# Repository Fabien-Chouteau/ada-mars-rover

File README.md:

This project now lives at https://github.com/AdaCore/mars-rover-demo

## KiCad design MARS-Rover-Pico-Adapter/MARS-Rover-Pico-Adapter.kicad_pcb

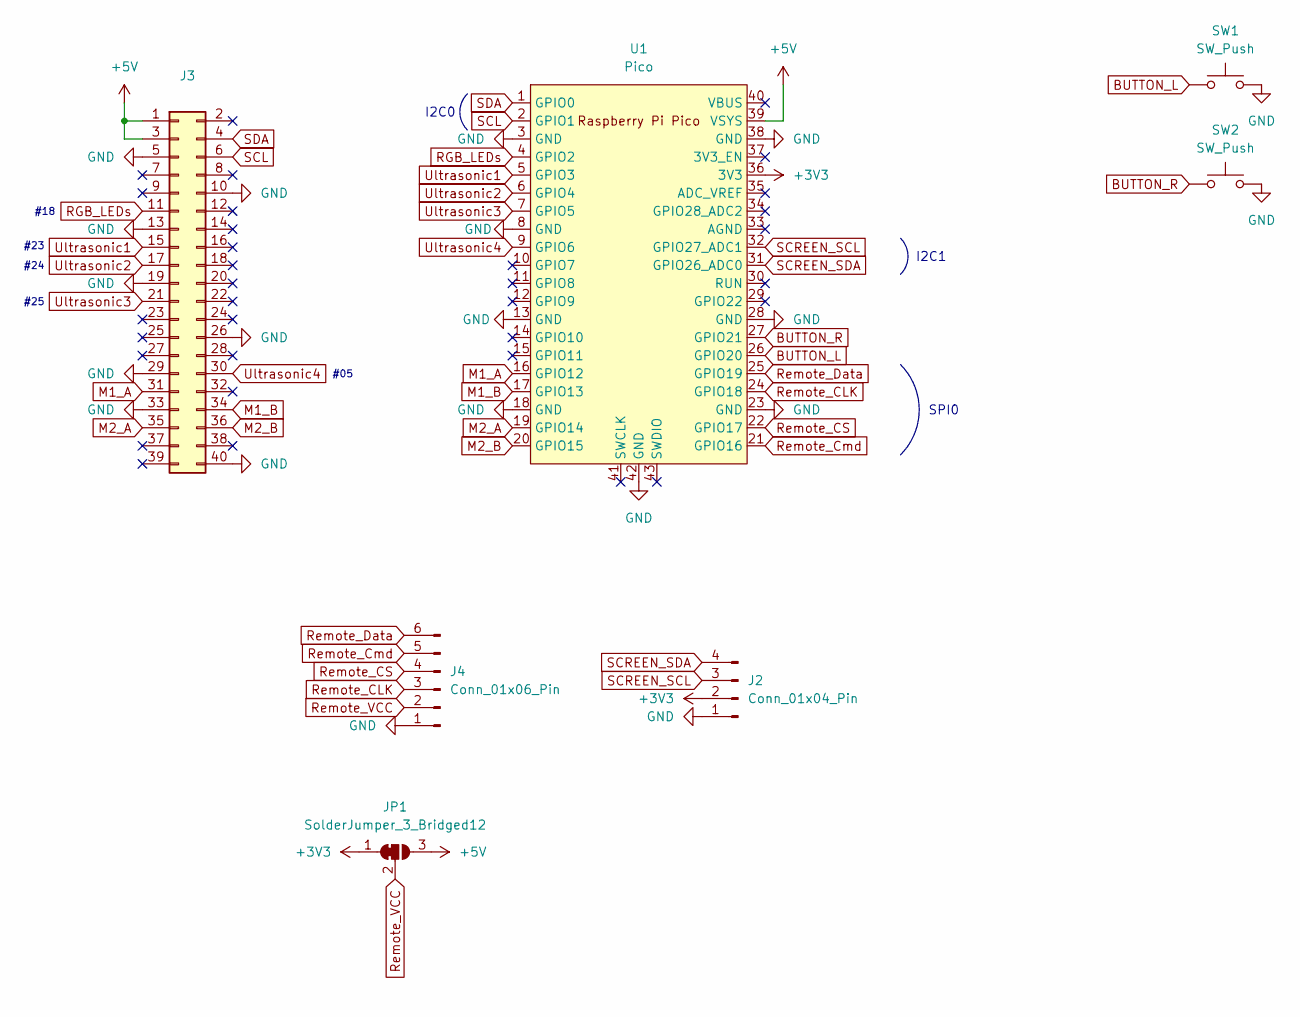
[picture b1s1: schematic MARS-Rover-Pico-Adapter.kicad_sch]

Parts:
J2: Conn_01x04_Pin; PinHeader_1x04_P2.54mm_Vertical
J3: Conn_02x20_Odd_Even; PinHeader_2x20_P2.54mm_Vertical
J4: Conn_01x06_Pin; PinHeader_1x06_P2.54mm_Vertical
JP1: SolderJumper_3_Bridged12; SolderJumper-3_P1.3mm_Bridged12_RoundedPad1.0x1.5mm
SW1, SW2: SW_Push; SW_PUSH_6mm
U1: Pico; RPi_Pico_SMD_TH

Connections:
+3V3: J2.2, JP1.1 (A), U1.36 (3V3)
+5V: J3.1, J3.3, JP1.3 (B), U1.39 (VSYS)
BUTTON_L: SW1.1, U1.26 (GPIO20)
BUTTON_R: SW2.1, U1.27 (GPIO21)
GND: J2.1, J3.5, J3.10, J3.13, J3.19, J3.26, J3.29, J3.33, J3.40, J4.1, SW1.2, SW2.2, U1.3 (GND), U1.8 (GND), U1.13 (GND), U1.18 (GND), U1.23 (GND), U1.28 (GND), U1.38 (GND), U1.42 (GND)
M1_A: J3.31, U1.16 (GPIO12)
M1_B: J3.34, U1.17 (GPIO13)
M2_A: J3.35, U1.19 (GPIO14)
M2_B: J3.36, U1.20 (GPIO15)
RGB_LEDs: J3.11, U1.4 (GPIO2)
Remote_CLK: J4.3, U1.24 (GPIO18)
Remote_CS: J4.4, U1.22 (GPIO17)
Remote_Cmd: J4.5, U1.21 (GPIO16)
Remote_Data: J4.6, U1.25 (GPIO19)
Remote_VCC: J4.2, JP1.2 (C)
SCL: J3.6, U1.2 (GPIO1)
SCREEN_SCL: J2.3, U1.32 (GPIO27_ADC1)
SCREEN_SDA: J2.4, U1.31 (GPIO26_ADC0)
SDA: J3.4, U1.1 (GPIO0)
Ultrasonic1: J3.15, U1.5 (GPIO3)
Ultrasonic2: J3.17, U1.6 (GPIO4)
Ultrasonic3: J3.21, U1.7 (GPIO5)
Ultrasonic4: J3.30, U1.9 (GPIO6)

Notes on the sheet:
I2C1
#24
SPI0
#18
#05
#23
I2C0
#25

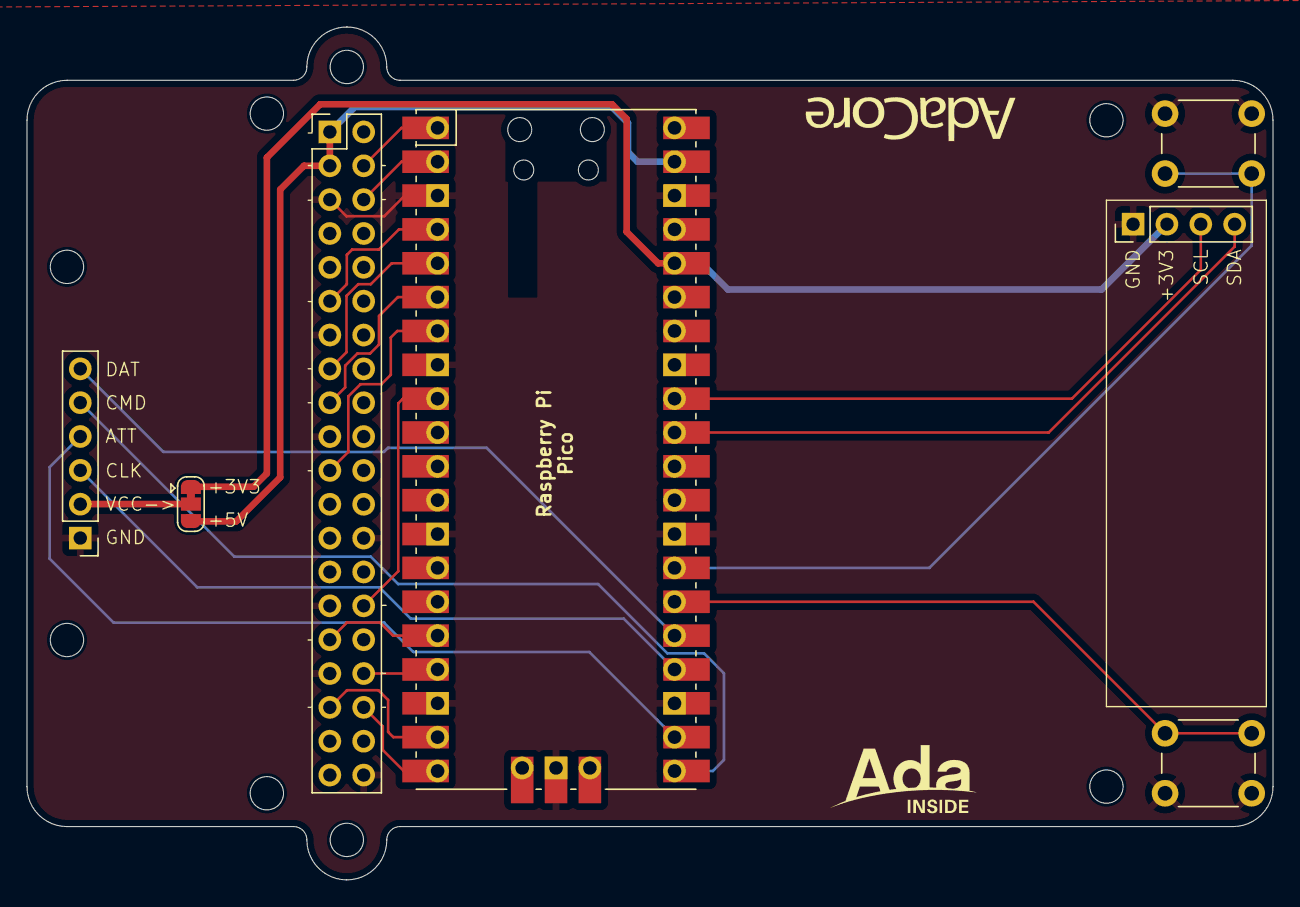
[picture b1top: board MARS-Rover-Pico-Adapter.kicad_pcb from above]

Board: 2 copper layers, 93.5 x 64.0 mm, 7 parts (0 on the bottom side), 23 nets.

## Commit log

2024-10-23 Pico Adapter v1.0
2025-02-12 Update adapter board
2025-02-26 Prove rover controllers cannot command a crash
    This commit introduces a formalization of the safety requirement:
    > The Mars Rover shall not proceed straight forward when the distance to
    > an obstacle is less than the Safety Threshold.
    via a new predicate named `Cannot_Crash`:
    ```ada
    function Cannot_Crash return Boolean is
2025-02-26 Switch sonar signal to a different pin
    (Provides more space for the mast to rotate)
2025-02-26 Adjust the range of mast rotation
2025-02-26 Add GUI to adjust steering wheels center point
2025-02-26 Add some debug/info message on the screen
2025-03-06 Add remote controller support binding package
2025-03-25 Fix steering direction when reversing
2025-03-25 Improve sensor mast control
    The sonar sensor reading greatly depends on the angle between the sensor
    and the obstacle surface. A shallow angle reduces the ability to detect
    an obstacle. It seems like the material of the obstacle also has an
    impact on this.
    To circumvent this limitation, we increase the rotation range and speed
    of the sensor mast.
2025-03-25 Robustify sonar measurement
2025-03-25 Increase range of motion for the mast
2025-06-24 Remove project
